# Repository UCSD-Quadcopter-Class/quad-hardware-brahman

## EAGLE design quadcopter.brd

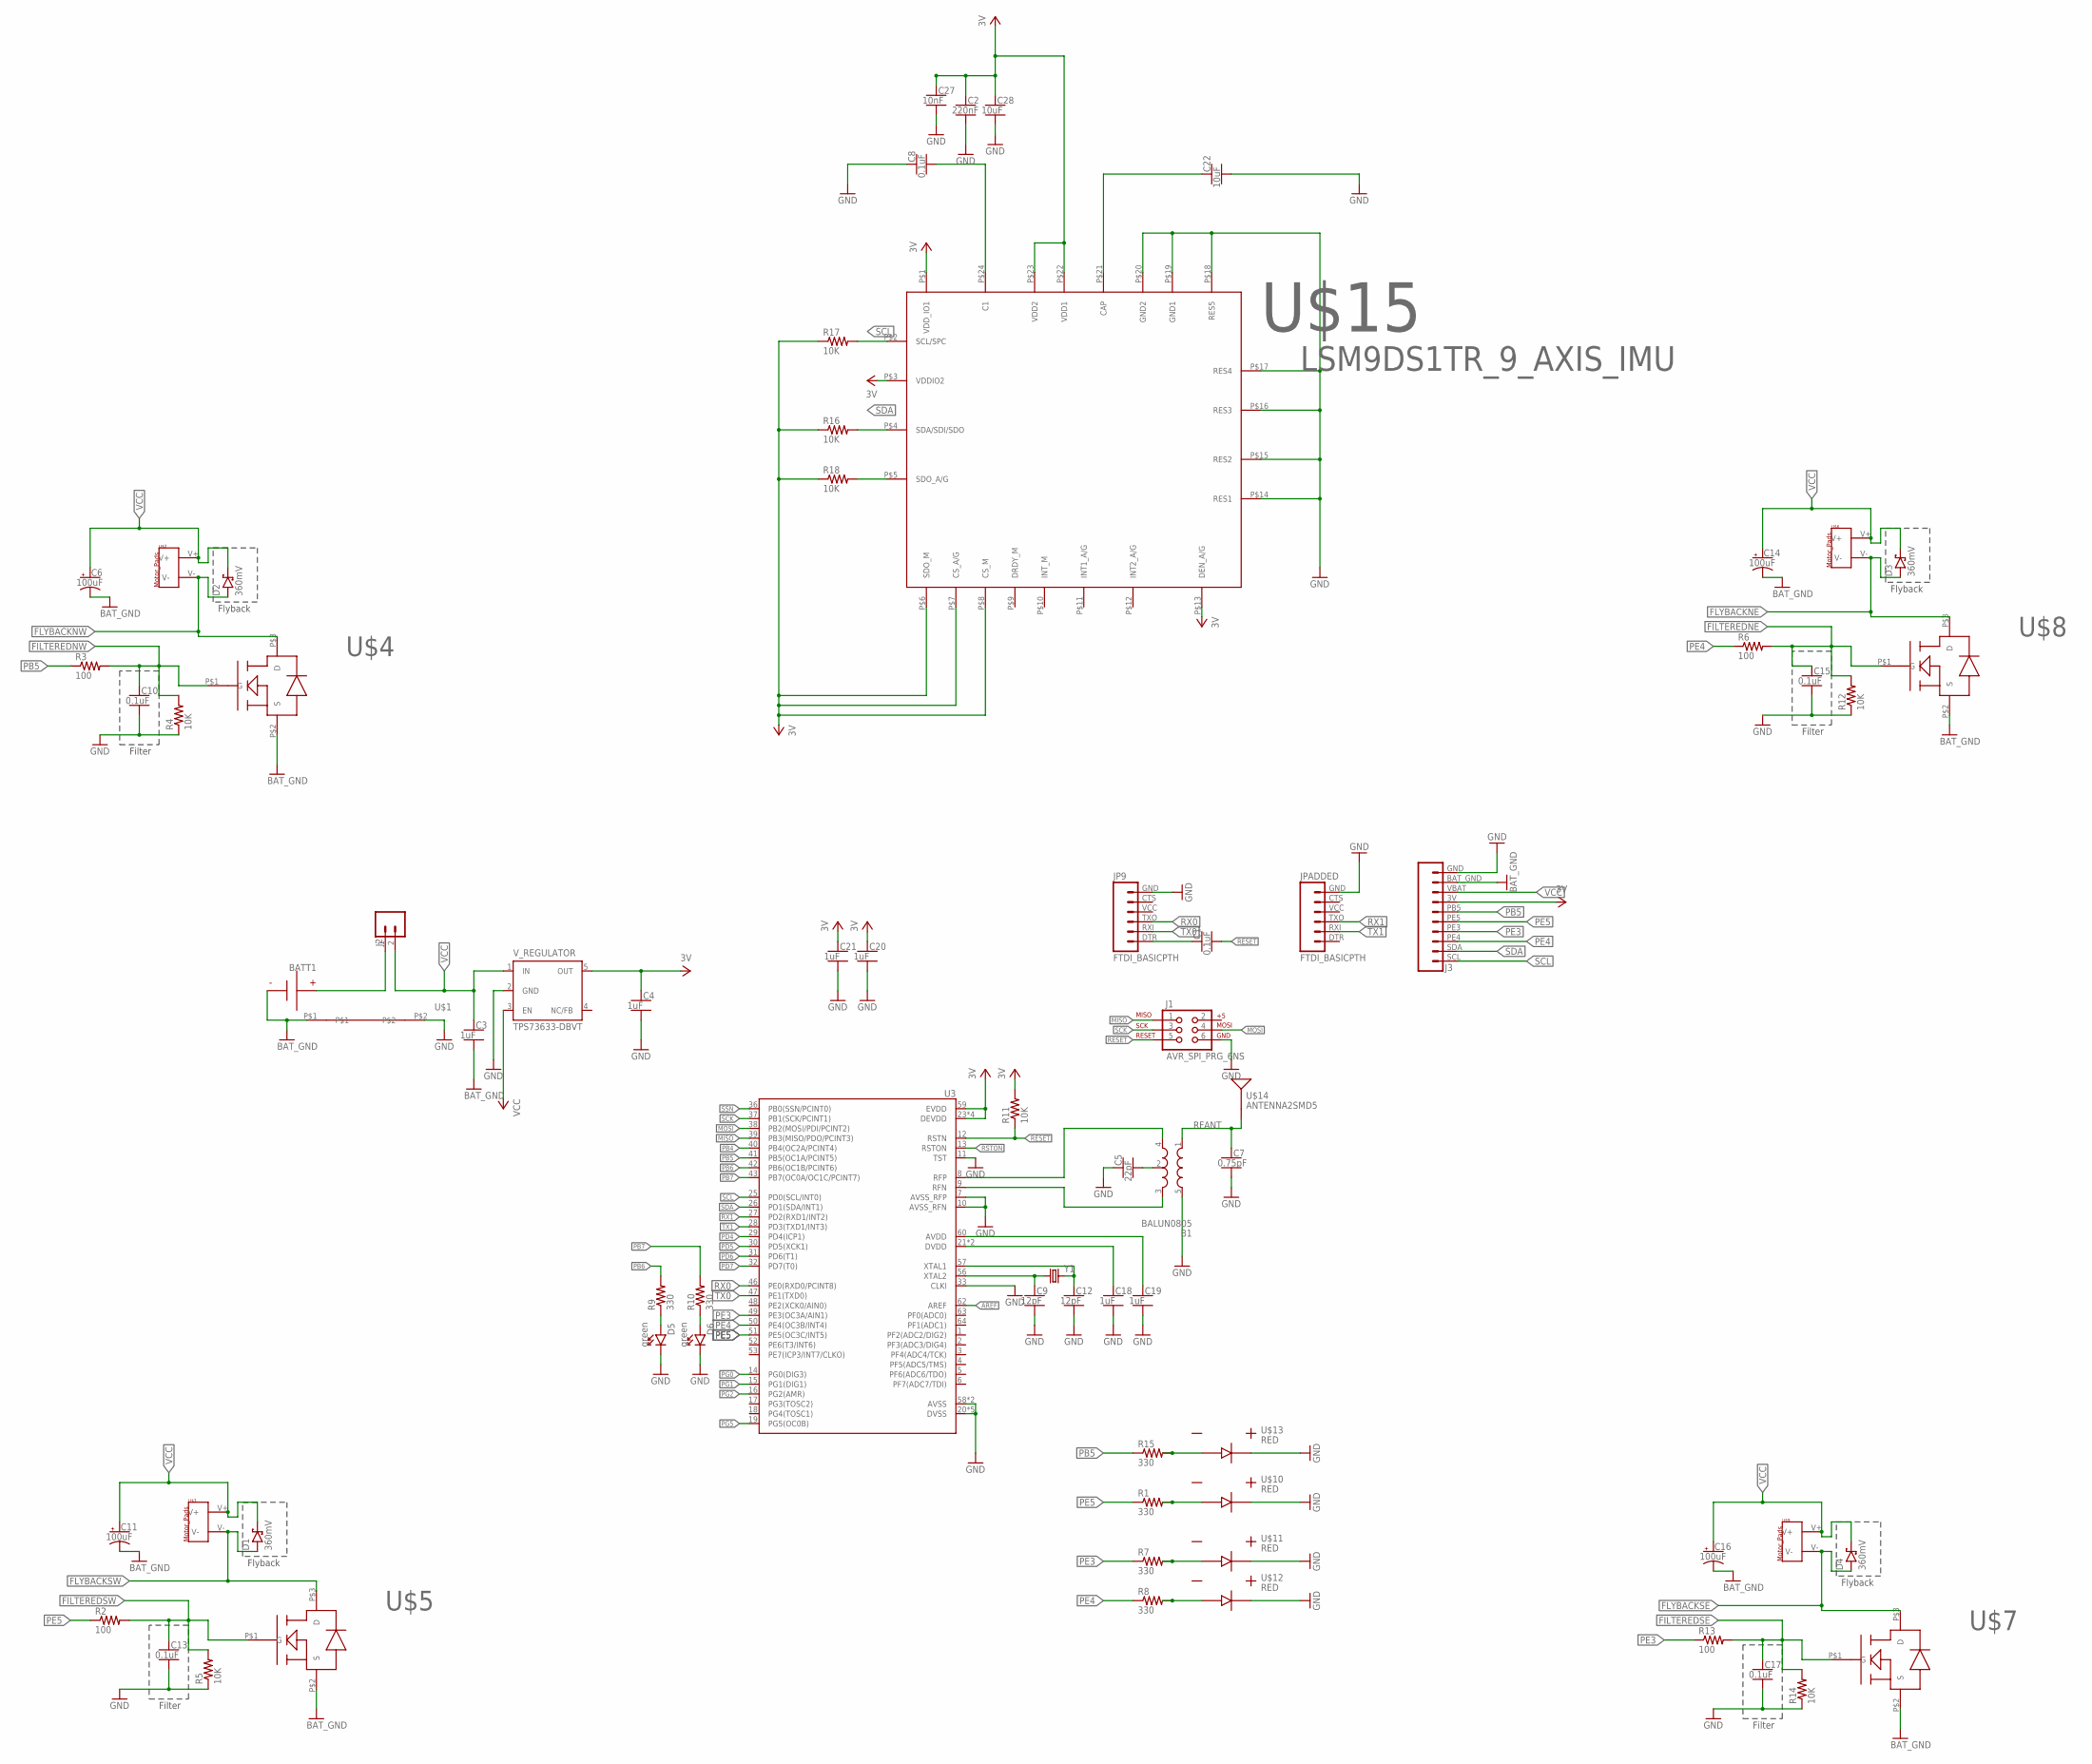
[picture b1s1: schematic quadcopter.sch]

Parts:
B1: BALUN0805; BALUN
BATT1: BATTERY-HUBSAN-W/HOLDER; BATTERY-W/HOLDER-380MAH-HUBSAN
C1, C8, C10, C13, C15, C17: 0.1uF; CAPC2012X140_HS
C2: 220nF; CAPC2012X140_HS
C3, C4, C18, C19, C20, C21: 1uF; CAPC2012X140_HS
C5: 22pF; CAPC2012X140_HS
C6, C11, C14, C16: 100uF; CAPMP7343X310_HS
C7: 0.75pF; CAPC2012X140_HS
C9, C12: 12pF; CAPC2012X140_HS
C22, C28: 10uF; CAPC2012X140_HS
C27: 10nF; CAPC2012X140_HS
D1, D2, D3, D4: 360mV; SOD3716X135_HS
D5, D6: green; LEDSC125X200X120-2_HS
J1: AVR_SPI_PRG_6NS; 2X3-NS
J2: MALE_HEADER_2POS-2X1-0.1IN; MALE_HEADER_2X1_0.1IN
J3: BREAKOUT_HEADERTH-254X10; HDRV10W63P254_10X1_2540X254H838_HS
JP9: FTDI_BASICPTH; FTDI_BASIC
JPADDED: FTDI_BASICPTH; FTDI_BASIC
R1, R7, R8, R9, R10, R15: 330; RESC2012X60_HS
R2, R3, R6, R13: 100; RESC2012X60_HS
R4, R5, R11, R12, R14, R16, R17, R18: 10K; RESC2012X60_HS
U3: ATMEGA128RFA1; QFN-64
U$1: NET_BRIDGE
U$2, U$3, U$6, U$9: MOTOR_PADS
U$4, U$5, U$7, U$8: N_CHANNEL_MOSFET; N-CHANNEL-MOSFET
U$10, U$11, U$12, U$13: RED; RED_LED
U$14: ANTENNA2SMD5; ANTENNA-CHIP5
U$15: LSM9DS1TR_9_AXIS_IMU
V_REGULATOR: TPS73633-DBVT; SOT23-DBV
Y1: CRYSTAL5X3; CRYSTAL-SMD-5X3

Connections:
3V: C2.1, C4.1, C20.1, C21.1, C27.1, C28.1, J3.3V, R11.2, R16.1, R17.1, R18.1, U3.23 (DEVDD), U3.34 (DEVDD), U3.44 (DEVDD), U3.54 (DEVDD), U3.59 (EVDD), U$15.P$1 (VDD_IO1), U$15.P$3 (VDDIO2), U$15.P$6 (SDO_M), U$15.P$7 (CS_A/G), U$15.P$8 (CS_M), U$15.P$13 (DEN_A/G), U$15.P$22 (VDD1), U$15.P$23 (VDD2), V_REGULATOR.5 (OUT)
AREF: U3.62 (AREF)
AVDD: C19.1, U3.60 (AVDD)
BAT_GND: BATT1.- (N), C3.2, C6.2 (-), C11.2 (-), C14.2 (-), C16.2 (-), J3.BAT_GND, U$1.P$1, U$4.P$2 (S), U$5.P$2 (S), U$7.P$2 (S), U$8.P$2 (S)
DVDD: C18.1, U3.21 (DVDD), U3.22 (DVDD)
FILTEREDNE: C15.1, R6.2, R12.2, U$8.P$1 (G)
FILTEREDNW: C10.1, R3.2, R4.2, U$4.P$1 (G)
FILTEREDSE: C17.1, R13.2, R14.2, U$7.P$1 (G)
FILTEREDSW: C13.1, R2.2, R5.2, U$5.P$1 (G)
FLYBACKNE: D3.A, U$6.V-, U$8.P$3 (D)
FLYBACKNW: D2.A, U$2.V-, U$4.P$3 (D)
FLYBACKSE: D4.A, U$7.P$3 (D), U$9.V-
FLYBACKSW: D1.A, U$3.V-, U$5.P$3 (D)
GND: B1.5 (GND), C2.2, C4.2, C5.1, C7.2, C8.1, C9.2, C10.2, C12.2, C13.2, C15.2, C17.2, C18.2, C19.2, C20.2, C21.2, C22.2, C27.2, C28.2, D5.C, D6.C, J1.6, J3.GND, JP9.GND (6), JPADDED.GND (6), R4.1, R5.1, R12.1, R14.1, U3.7 (AVSS_RFP), U3.10 (AVSS_RFN), U3.11 (TST), U3.20 (DVSS), U3.24 (DVSS), U3.33 (CLKI), U3.35 (DVSS), U3.45 (DVSS), U3.55 (DVSS), U3.58 (AVSS), U3.61 (AVSS), U$1.P$2, U$10.P$3 (PAS_POS), U$11.P$3 (PAS_POS), U$12.P$3 (PAS_POS), U$13.P$3 (PAS_POS), U$15.P$14 (RES1), U$15.P$15 (RES2), U$15.P$16 (RES3), U$15.P$17 (RES4), U$15.P$18 (RES5), U$15.P$19 (GND1), U$15.P$20 (GND2), V_REGULATOR.2 (GND)
MISO: J1.1, U3.39 (PB3(MISO/PDO/PCINT3))
MOSI: J1.4, U3.38 (PB2(MOSI/PDI/PCINT2))
unnamed: R1.2, U$10.P$1 (PAS_NEG)
unnamed: C12.1, U3.57 (XTAL1), Y1.3 (2)
unnamed: C9.1, U3.56 (XTAL2), Y1.1
unnamed: R7.2, U$11.P$1 (PAS_NEG)
unnamed: BATT1.+, J2.1
unnamed: B1.2 (GND), C5.2
unnamed: D5.A, R9.1
unnamed: R8.2, U$12.P$1 (PAS_NEG)
unnamed: R18.2, U$15.P$5 (SDO_A/G)
unnamed: R15.2, U$13.P$1 (PAS_NEG)
unnamed: D6.A, R10.1
unnamed: C8.2, U$15.P$24 (C1)
unnamed: C22.1, U$15.P$21 (CAP)
unnamed: C1.1, JP9.DTR (1)
PB4: U3.40 (PB4(OC2A/PCINT4))
PB5: J3.PB5, R3.1, R15.1, U3.41 (PB5(OC1A/PCINT5))
PB6: R9.2, U3.42 (PB6(OC1B/PCINT6))
PB7: R10.2, U3.43 (PB7(OC0A/OC1C/PCINT7))
PD4: U3.29 (PD4(ICP1))
PD5: U3.30 (PD5(XCK1))
PD6: U3.31 (PD6(T1))
PD7: U3.32 (PD7(T0))
PE3: J3.PE3, R7.1, R13.1, U3.49 (PE3(OC3A/AIN1))
PE4: J3.PE4, R6.1, R8.1, U3.50 (PE4(OC3B/INT4))
PE5: J3.PE5 (P5), R1.1, R2.1, U3.51 (PE5(OC3C/INT5))
PG0: U3.14 (PG0(DIG3))
PG1: U3.15 (PG1(DIG1))
PG2: U3.16 (PG2(AMR))
PG5: U3.19 (PG5(OC0B))
RESET: C1.2, J1.5, R11.1, U3.12 (RSTN)
RFANT: B1.1 (IN), C7.1, U$14.FEED
RFN: B1.3 (OUT2), U3.9 (RFN)
RFP: B1.4 (OUT1), U3.8 (RFP)
RSTON: U3.13 (RSTON)
RX0: JP9.TXO (3), U3.46 (PE0(RXD0/PCINT8))
RX1: JPADDED.TXO (3), U3.27 (PD2(RXD1/INT2))
SCK: J1.3, U3.37 (PB1(SCK/PCINT1))
SCL: J3.SCL, R17.2, U3.25 (PD0(SCL/INT0)), U$15.P$2 (SCL/SPC)
SDA: J3.SDA, R16.2, U3.26 (PD1(SDA/INT1)), U$15.P$4 (SDA/SDI/SDO)
SSN: U3.36 (PB0(SSN/PCINT0))
TX0: JP9.RXI (2), U3.47 (PE1(TXD0))
TX1: JPADDED.RXI (2), U3.28 (PD3(TXD1/INT3))
VCC: C3.1, C6.1 (+), C11.1 (+), C14.1 (+), C16.1 (+), D1.C, D2.C, D3.C, D4.C, J2.2, J3.VBAT, U$2.V+, U$3.V+, U$6.V+, U$9.V+, V_REGULATOR.1 (IN), V_REGULATOR.3 (EN)

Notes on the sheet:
Filter
Flyback

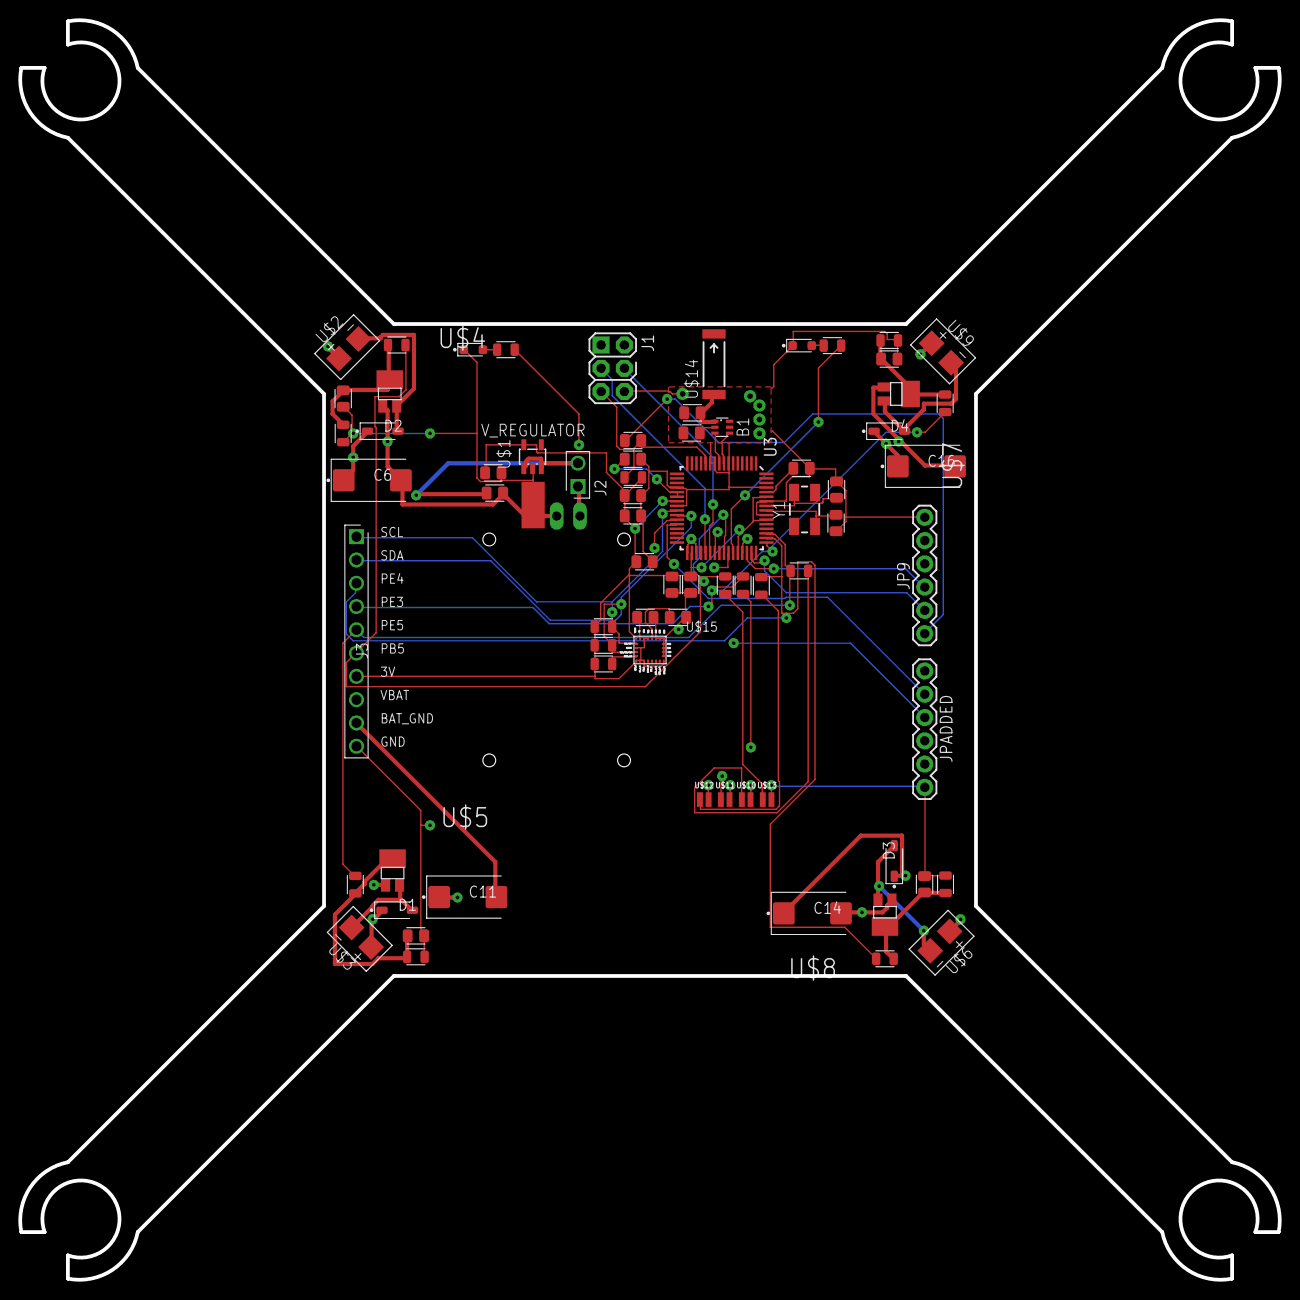
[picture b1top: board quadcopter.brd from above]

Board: 4 copper layers, 137.4 x 137.4 mm, 73 parts (1 on the bottom side), 47 nets.

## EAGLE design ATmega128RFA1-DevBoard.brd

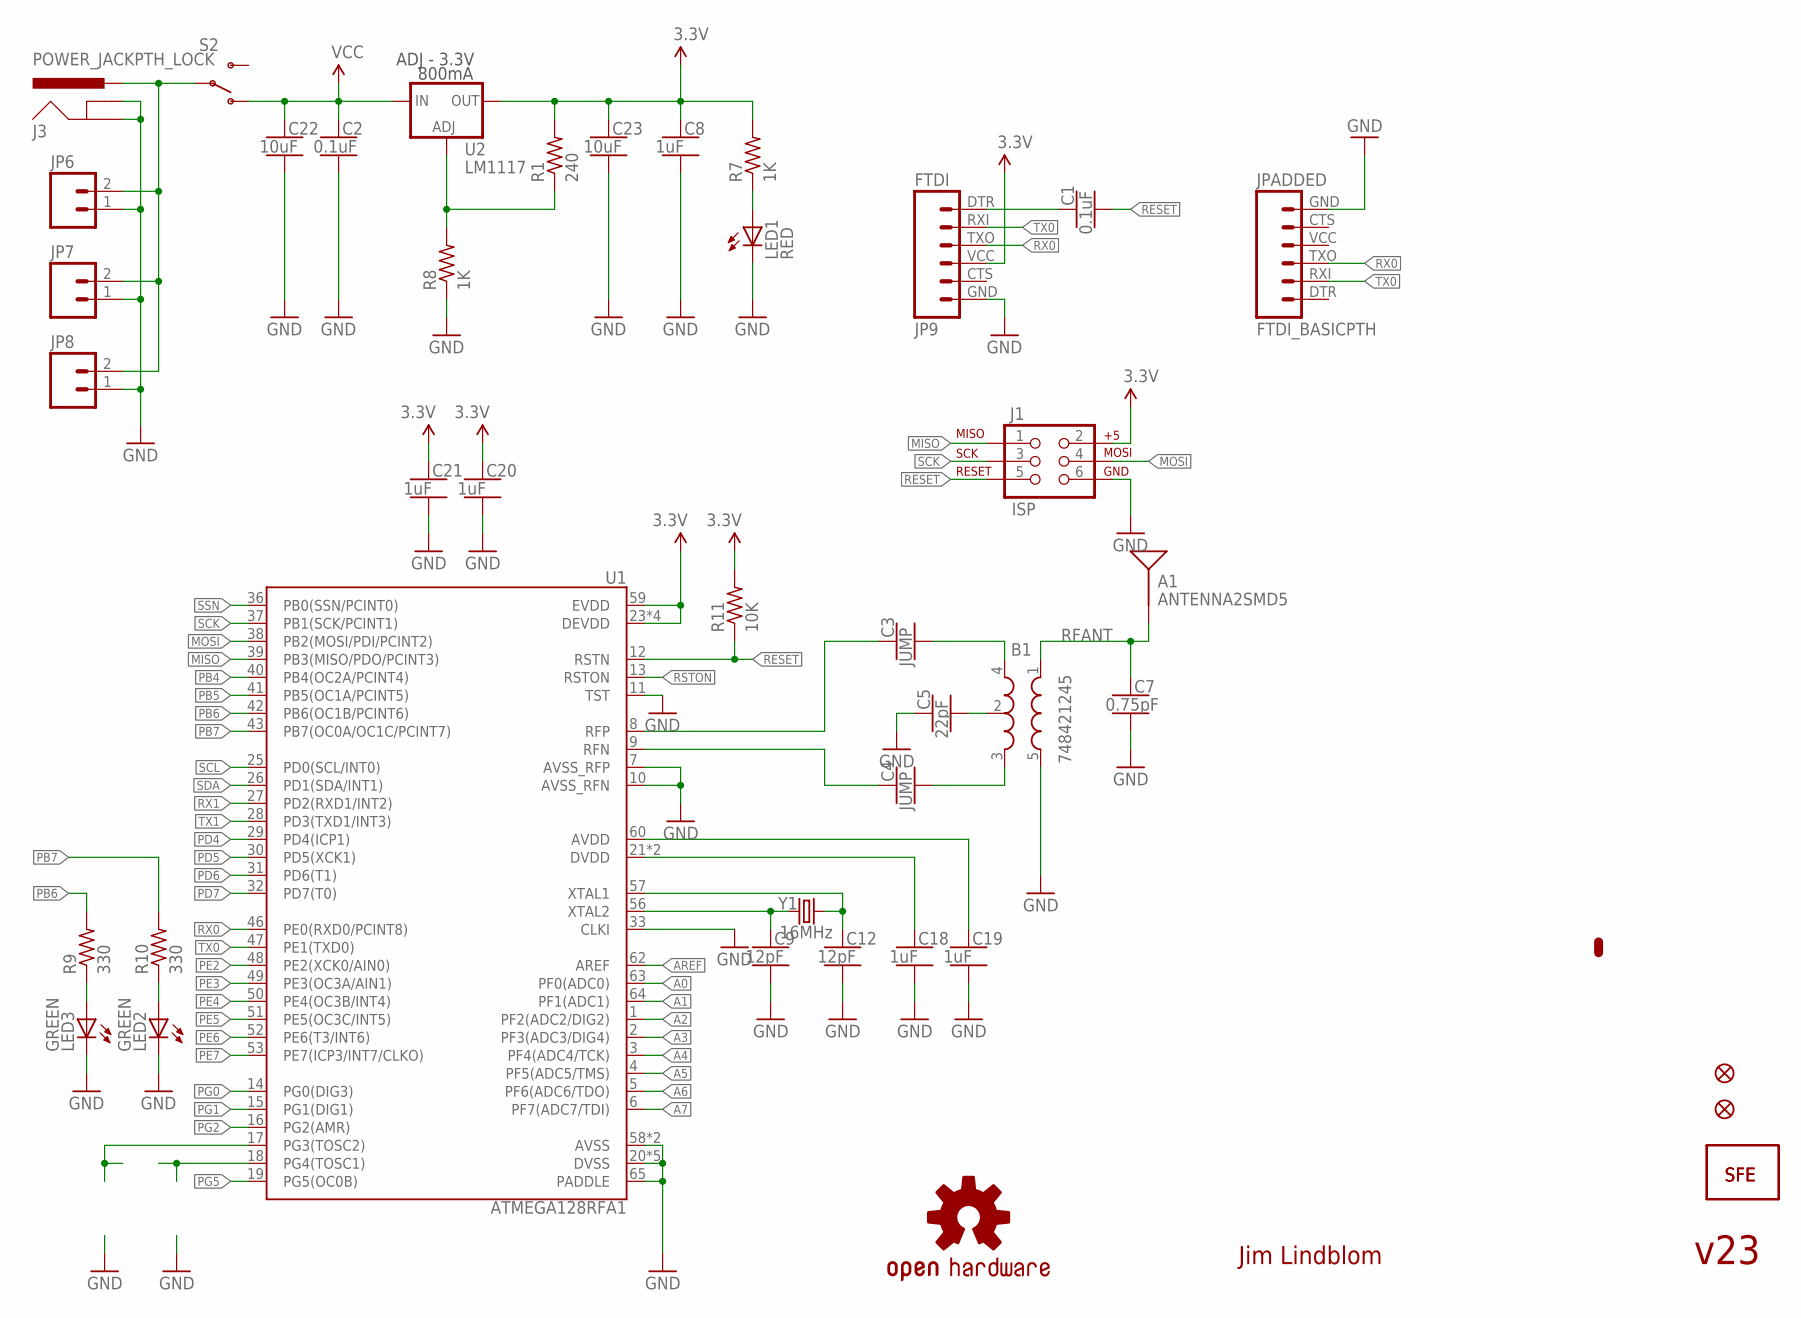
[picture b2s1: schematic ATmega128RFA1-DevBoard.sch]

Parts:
A1: ANTENNA2SMD5; ANTENNA-CHIP5
B1: 748421245; BALUN
C1, C2: 0.1uF; CAPC2012X140_HS
C3, C4: JUMP; CAPC2012X140_HS
C5: 22pF; CAPC2012X140_HS
C7: 0.75pF; CAPC2012X140_HS
C8, C18, C19, C20, C21: 1uF; CAPC2012X140_HS
C9, C12: 12pF; CAPC2012X140_HS
C22, C23: 10uF; CAPC2012X140_HS
FID1, FID2: FIDUCIALUFIDUCIAL; MICRO-FIDUCIAL
J1: ISP; 2X3-NS
J3: POWER_JACKPTH_LOCK; POWER_JACK_PTH_LOCK
JP4, JP10: LOGO-SFENEW; SFE-NEW-WEBLOGO
JP6: M02JST-PTH-2; JST-2-PTH
JP7: M021X02_NO_SILK; 1X02_NO_SILK
JP8: M023.5MM-NO_SILK; SCREWTERMINAL-3.5MM-2-NS
JP9: FTDI; FTDI_BASIC
JPADDED: FTDI_BASICPTH; FTDI_BASIC
LED1: RED; LED-0603
LED2, LED3: GREEN; LED-0603
R1: 240; RESC2012X60_HS
R7, R8: 1K; RESC2012X60_HS
R9, R10: 330; RESC2012X60_HS
R11: 10K; RESC2012X60_HS
S2: SWITCH-SPST-SMD-A
U1: ATMEGA128RFA1; QFN-64
U2: LM1117; SOT223
U$1: OSHW-LOGOS; OSHW-LOGO-S
Y1: 16MHz; CRYSTAL-SMD-5X3

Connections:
3.3V: C8.1, C20.1, C21.1, C23.1, J1.2, JP9.VCC (4), R1.2, R7.2, R11.2, U1.23 (DEVDD), U1.34 (DEVDD), U1.44 (DEVDD), U1.54 (DEVDD), U1.59 (EVDD), U2.2 (OUT)
A0: U1.63 (PF0(ADC0))
A1: U1.64 (PF1(ADC1))
A2: U1.1 (PF2(ADC2/DIG2))
A3: U1.2 (PF3(ADC3/DIG4))
A4: U1.3 (PF4(ADC4/TCK))
A5: U1.4 (PF5(ADC5/TMS))
A6: U1.5 (PF6(ADC6/TDO))
A7: U1.6 (PF7(ADC7/TDI))
AREF: U1.62 (AREF)
AVDD: C19.1, U1.60 (AVDD)
DTR: C1.1, JP9.DTR (1)
DVDD: C18.1, U1.21 (DVDD), U1.22 (DVDD)
FB: R1.1, R8.2, U2.1 (ADJ)
GND: B1.5 (GND), C2.2, C5.1, C7.2, C8.2, C9.2, C12.2, C18.2, C19.2, C20.2, C21.2, C22.2, C23.2, J1.6, J3.GND, J3.GNDBREAK, JP6.1, JP7.1, JP8.1, JP9.GND (6), JPADDED.GND (6), LED1.C, LED2.C, LED3.C, R8.1, U1.7 (AVSS_RFP), U1.10 (AVSS_RFN), U1.11 (TST), U1.20 (DVSS), U1.24 (DVSS), U1.33 (CLKI), U1.35 (DVSS), U1.45 (DVSS), U1.55 (DVSS), U1.58 (AVSS), U1.61 (AVSS), U1.65 (PADDLE)
MISO: J1.1, U1.39 (PB3(MISO/PDO/PCINT3))
MOSI: J1.4, U1.38 (PB2(MOSI/PDI/PCINT2))
unnamed: LED1.A, R7.1
unnamed: C12.1, U1.57 (XTAL1), Y1.3 (2)
unnamed: C9.1, U1.56 (XTAL2), Y1.1
unnamed: B1.2 (GND), C5.2
unnamed: LED3.A, R9.1
unnamed: J3.PWR, JP6.2, JP7.2, JP8.2, S2.2
unnamed: B1.4 (OUT1), C3.2
unnamed: B1.3 (OUT2), C4.2
unnamed: LED2.A, R10.1
PB4: U1.40 (PB4(OC2A/PCINT4))
PB5: U1.41 (PB5(OC1A/PCINT5))
PB6: R9.2, U1.42 (PB6(OC1B/PCINT6))
PB7: R10.2, U1.43 (PB7(OC0A/OC1C/PCINT7))
PD4: U1.29 (PD4(ICP1))
PD5: U1.30 (PD5(XCK1))
PD6: U1.31 (PD6(T1))
PD7: U1.32 (PD7(T0))
PE2: U1.48 (PE2(XCK0/AIN0))
PE3: U1.49 (PE3(OC3A/AIN1))
PE4: U1.50 (PE4(OC3B/INT4))
PE5: U1.51 (PE5(OC3C/INT5))
PE6: U1.52 (PE6(T3/INT6))
PE7: U1.53 (PE7(ICP3/INT7/CLKO))
PG0: U1.14 (PG0(DIG3))
PG1: U1.15 (PG1(DIG1))
PG2: U1.16 (PG2(AMR))
PG5: U1.19 (PG5(OC0B))
RESET: C1.2, J1.5, R11.1, U1.12 (RSTN)
RFANT: A1.FEED, B1.1 (IN), C7.1
RFN: C4.1, U1.9 (RFN)
RFP: C3.1, U1.8 (RFP)
RSTON: U1.13 (RSTON)
RX0: JP9.TXO (3), U1.46 (PE0(RXD0/PCINT8))
RX1: U1.27 (PD2(RXD1/INT2))
SCK: J1.3, U1.37 (PB1(SCK/PCINT1))
SCL: U1.25 (PD0(SCL/INT0))
SDA: U1.26 (PD1(SDA/INT1))
SSN: U1.36 (PB0(SSN/PCINT0))
TX0: JP9.RXI (2), U1.47 (PE1(TXD0))
TX1: U1.28 (PD3(TXD1/INT3))
VCC: C2.1, C22.1, S2.1 (O), U2.3 (IN)

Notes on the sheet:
Jim Lindblom
800mA
ADJ - 3.3V
v23

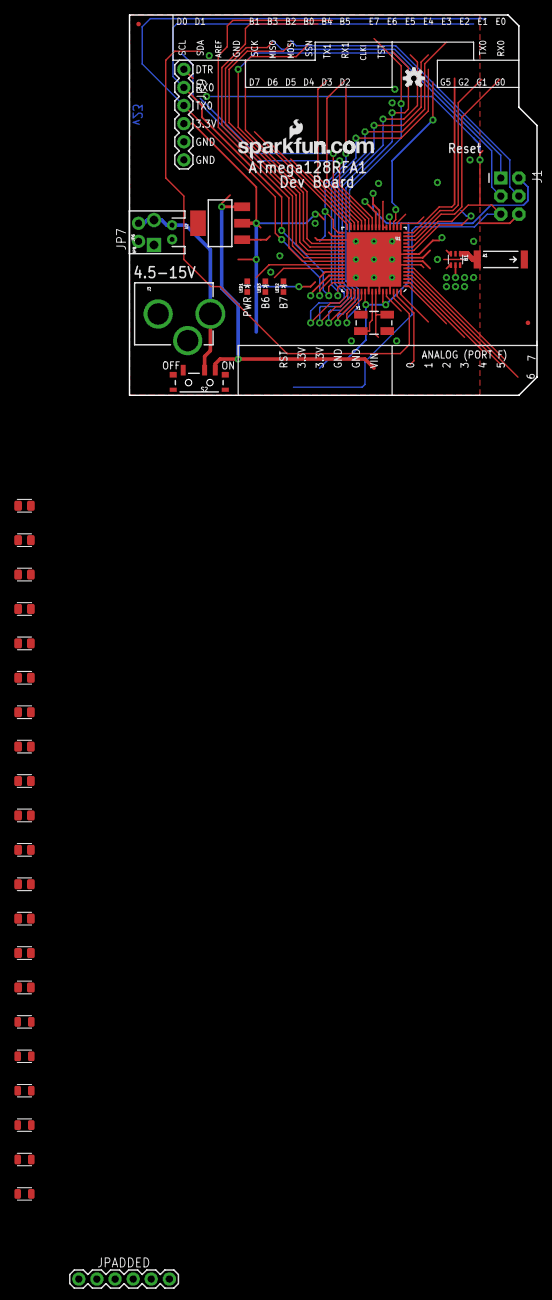
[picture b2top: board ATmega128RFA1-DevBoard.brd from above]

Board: 2 copper layers, 57.1 x 53.3 mm, 42 parts (1 on the bottom side), 27 nets.

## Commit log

2017-04-16 My lbr
2017-04-16 added brandon's library
2017-04-16 imu/motor drive/microcontroller added
    need to ask prof questions and do powersupply/leds/breakout header
2017-04-20 lab 4 complete
2017-04-20 adding LED data sheet
2017-04-25 added design questions
2017-04-25 added their questions
2017-04-25 adding their reviews
2017-04-27 instructior review of original schematic
2017-05-01 finished lab 7
2017-05-04 added board review questions
2017-05-11 adding their questions about our board
2017-05-14 more schematic comments from swanson
2017-05-15 made changes to schematic/board per the comments the prof made
2017-05-16 schematic changes for prof
2017-05-16 more changes made to board/schematic
2017-05-17 schematic and board no longer inconsistent
2017-05-18 made changes to pour
    need to change RED LED to be more like data sheet
2017-05-23 made changes to board, almost done.
2017-05-24 almost done with board, have 3 airwires
2017-05-25 board 100% routed
2017-05-25 added faraday cage to antenna
2017-05-25 fixed crystal routing and antenna routing, moved motor recouping caps, and replaced wrong filter diodes
2017-05-25 fixed mosfet padding, rerouted, added gerber files

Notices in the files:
parts and their libraries:
SparkFun-DigitalIC: Licensing: CC v3.0 Share-Alike You are welcome to use this library for commercial purposes.
SparkFun-Aesthetics: Released under the Creative Commons
SparkFun-Aesthetics: http://creativecommons.org/licenses/by-sa/3.0
